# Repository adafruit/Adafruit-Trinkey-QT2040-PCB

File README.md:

## Adafruit Trinkey QT2040 PCB

<a href="http://www.adafruit.com/products/5056"><br/>
Click here to purchase one from the Adafruit shop</a>

PCB files for the Adafruit Trinkey QT2040. 

Format is EagleCAD schematic and board layout
* https://www.adafruit.com/product/5056

### Description

It's half USB Key, half Adafruit QT Py, and a lotta RP2040...it's Trinkey QT2040, the circuit board with an RP2040 heart and Stemma QT legs. Folks are loving the QT Py 2040 we made, but maybe you want something plug-and-play. So we thought, hey what if we made something like that plugs right into your computer's USB port? And this is what we came up with!

The PCB is designed to slip into any USB A port on a computer or laptop. There's an RP2040 microcontroller on board with just enough circuitry to keep it happy. There's an RGB NeoPixel, a reset and bootloader or user button and a STEMMA QT Port on the end. That's it!

With the body of the board being 1.0" x 0.7" and four mounting holes, you can attach just about any of our QT boards right on (some are a little larger so just check that has the holes in the same locations). Use M2.5 sized standoffs and screws to do so, you could use 2 diagonal at a minimum. Then use a shorty QT cable and you've got a custom sensor Trinkey for any sensor purpose.

The board comes with 8 MB of QSPI flash memory so you can put all of our CircuitPython drivers on the disk!

#### Plug-and-play STEMMA QT

One of the stars of this board is our favorite connector - the STEMMA QT, a chainable I2C port that can be used with any of our STEMMA QT sensors and accessories. Having this connector means you don't need to do any soldering to get started.

What can you pop into the QT port? How about OLEDs! Inertial Measurement Units! Sensors a-plenty. All plug-and-play thanks to the innovative chainable design: SparkFun Qwiic-compatible STEMMA QT connectors for the I2C bus so you don't even need to solder. Just plug in a compatible cable and attach it to your MCU of choice, and you’re ready to load up some software and measure some light.

Use any SparkFun Qwiic boards! Seeed Grove I2C boards will also work with this adapter cable.

#### Software Support

At the time of launch, there is no Arduino core support for the chip on this board. There is great C/C++ support, an official MicroPython port, and a CircuitPython port! We of course recommend CircuitPython because we think it's the easiest way to get started and it has support with most of our drivers, displays, sensors, and more, supported out of the box so you can follow along with our CircuitPython projects and tutorials.

While the RP2040 has lots of onboard RAM (264KB), it does not have built-in FLASH memory. Instead, that is provided by the external QSPI flash chip. On this board there is 8MB, which is shared between the program it's running and any file storage used by MicroPython or CircuitPython. When using C/C++ you get the whole flash memory, if using Python you will have about 7 MB remaining for code, files, images, fonts, etc.

* Main body is same size/mounting holes as most of our Stemma QT boards (1.0" x 0.7" with M2.5 holes)
* USB Type A connector with extra-thick PCB to fit into a USB host port
* RP2040 32-bit Cortex M0+ dual-core running at ~125 MHz @ 3.3V logic and power
* 264 KB RAM
* 8 MB SPI FLASH chip for storing files and CircuitPython/MicroPython code storage. No EEPROM
* Native USB supported by every OS - can be used as USB serial console, MIDI, Keyboard/Mouse HID, even a little disk drive for storing Python scripts.
* Can be used with MicroPython or CircuitPython
* Built-in RGB NeoPixel LED
* STEMMA QT / Qwiic port for I2C connectivity
* 3.3V regulator with 600mA peak output
* 12 MHz crystal
* Both Reset button and Bootloader select buttons for quick restarts (no unplugging-replugging to relaunch code)
* Bootloader button can also be safely used in 'user' code

#### About the RP2040

Inside the RP2040 is a 'permanent ROM' USB UF2 bootloader. What that means is when you want to program new firmware, you can hold down the BOOT button while plugging it into USB (or pulling down the RUN/Reset pin to ground) and it will appear as a USB disk drive you can drag the firmware onto. Folks who have been using Adafruit products will find this very familiar - we use the technique on all our native-USB boards. Just note you don't double-click reset, instead hold down the BOOT button during boot to enter the bootloader!

The RP2040 is a powerful chip, which has the clock speed of our M4 (SAMD51), and two cores that are equivalent to our M0 (SAMD21). Since it is an M0 chip, it does not have a floating point unit or DSP hardware support - so if you're doing something with heavy floating point math, it will be done in software and thus not as fast as an M4. For many other computational tasks, you'll get close-to-M4 speeds!

### License

Adafruit invests time and resources providing this open source design, please support Adafruit and open-source hardware by purchasing products from [Adafruit](https://www.adafruit.com)!

Designed by Limor Fried/Ladyada for Adafruit Industries.

Creative Commons Attribution/Share-Alike, all text above must be included in any redistribution. 
See license.txt for additional details.

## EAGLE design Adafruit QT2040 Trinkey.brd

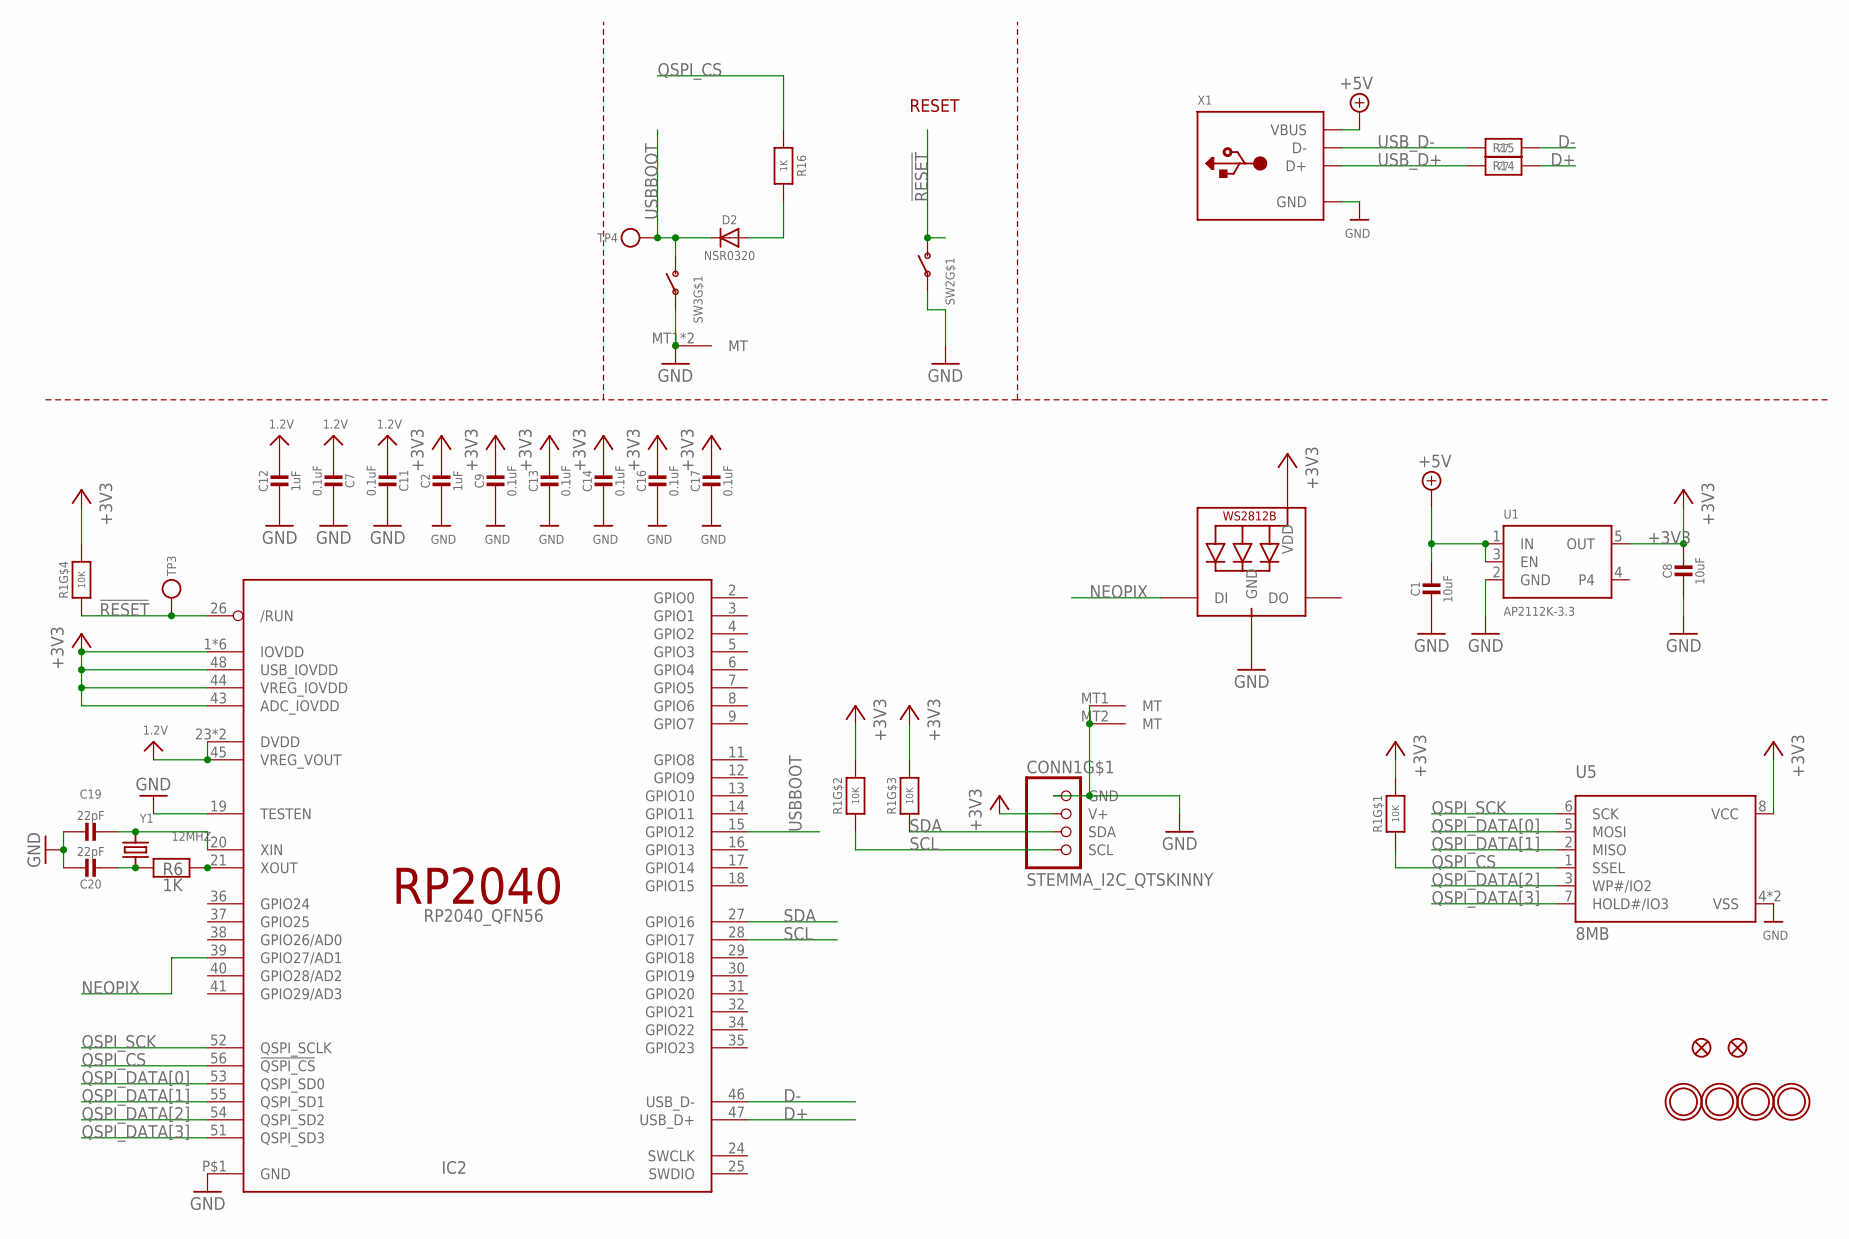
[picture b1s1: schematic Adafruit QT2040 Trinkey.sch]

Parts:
C1, C8: 10uF; 0805-NO
C2, C12: 1uF; 0603-NO
C7: 0.1uF; _0603MP
C9, C11, C13, C14, C16, C17: 0.1uF; 0603-NO
C19, C20: 22pF; 0603-NO
CONN1: STEMMA_I2C_QTSKINNY; JST_SH4_SKINNY
D2: NSR0320; SOD-323_MINI
IC2: RP2040_QFN56; QFN56_7MM_REDUCEDEPAD
LED1: WS2812B_SK6805_1515; SK6805_1515
R1: 10K; RESPACK_4X0603
R6, R16: 1K; 0603-NO
R14, R15: 27; 0603-NO
SW2, SW3: SWITCH_SPST_TACT_RA; SPST_TACTILE_RA
TP3, TP4: TESTPOINTROUND1.5MMNO; TESTPOINT_ROUND_1.5MM_NO
U1: AP2112K-3.3; SOT23-5
U5: 8MB; USON8_4X4
U$1, U$2, U$4, U$5: MOUNTINGHOLE2.5; MOUNTINGHOLE_2.5_PLATED
U$6, U$8: FIDUCIAL_1MM
X1: USB_TYPEAPCB; USBA_PCB
Y1: 12MHZ; CRYSTAL_2.5X2

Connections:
1.2V: C7.2, C11.2, C12.1, IC2.23 (DVDD), IC2.45 (VREG_VOUT), IC2.50 (DVDD)
!RESET: IC2.26 (/RUN), R1.4 (1), SW2.2 (S), TP3.P$1
+3V3: C2.1, C8.1, C9.1, C13.1, C14.1, C16.1, C17.1, CONN1.2 (V+), IC2.1 (IOVDD), IC2.10 (IOVDD), IC2.22 (IOVDD), IC2.33 (IOVDD), IC2.42 (IOVDD), IC2.43 (ADC_IOVDD), IC2.44 (VREG_IOVDD), IC2.48 (USB_IOVDD), IC2.49 (IOVDD), LED1.2 (VDD), R1.5 (2), R1.6 (2), R1.7 (2), R1.8 (2), U1.5 (OUT), U5.8 (VCC)
+5V: C1.1, U1.1 (IN), U1.3 (EN), X1.VCC (VBUS)
D+: IC2.47 (USB_D+), R15.2
D-: IC2.46 (USB_D-), R14.2
GND: C1.2, C2.2, C7.1, C8.2, C9.2, C11.1, C12.2, C13.2, C14.2, C16.2, C17.2, C19.1, C20.1, CONN1.1 (GND), CONN1.MT1 (MT), CONN1.MT2 (MT), IC2.19 (TESTEN), IC2.P$1 (GND), LED1.4 (GND), SW2.1, SW3.1, SW3.MT1 (MT), SW3.MT2 (MT), U1.2 (GND), U5.4 (VSS), U5.PAD (VSS), X1.GND
unnamed: D2.A, R16.2
unnamed: C19.2, IC2.20 (XIN), Y1.3 (2)
unnamed: C20.2, R6.1, Y1.1
unnamed: IC2.21 (XOUT), R6.2
NEOPIX: IC2.39 (GPIO27/AD1), LED1.1 (DI)
QSPI_CS: IC2.56 (!QSPI_CS), R1.1, R16.1, U5.1 (SSEL)
QSPI_DATA[0]: IC2.53 (QSPI_SD0), U5.5 (MOSI)
QSPI_DATA[1]: IC2.55 (QSPI_SD1), U5.2 (MISO)
QSPI_DATA[2]: IC2.54 (QSPI_SD2), U5.3 (WP#/IO2)
QSPI_DATA[3]: IC2.51 (QSPI_SD3), U5.7 (HOLD#/IO3)
QSPI_SCK: IC2.52 (QSPI_SCLK), U5.6 (SCK)
SCL: CONN1.4 (SCL), IC2.28 (GPIO17), R1.2 (1)
SDA: CONN1.3 (SDA), IC2.27 (GPIO16), R1.3 (1)
USBBOOT: D2.C, IC2.15 (GPIO12), SW3.2 (S), TP4.P$1
USB_D+: R15.1, X1.USB_PLUS (D+)
USB_D-: R14.1, X1.USB_NEG (D-)

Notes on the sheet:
RESET

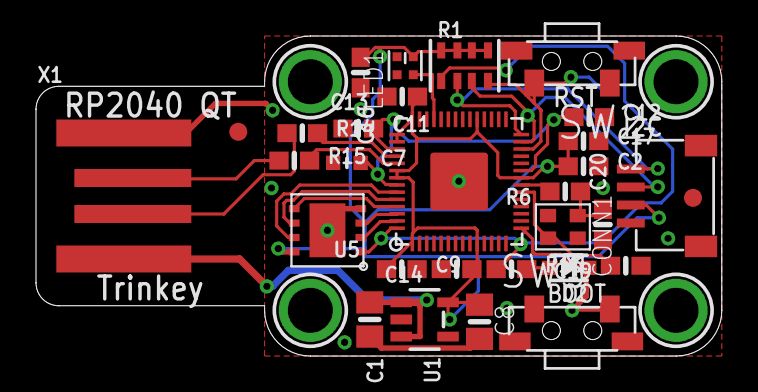
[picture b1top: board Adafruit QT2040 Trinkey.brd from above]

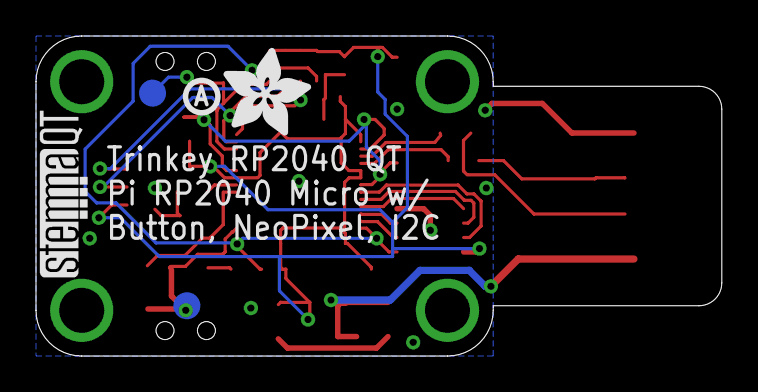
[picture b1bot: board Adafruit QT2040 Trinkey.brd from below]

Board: 2 copper layers, 38.1 x 17.8 mm, 39 parts (5 on the bottom side), 23 nets.

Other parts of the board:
U$7: STEMMAQT
U$9: PCBFEAT-REV-040
U$10: ADAFRUIT_5MM

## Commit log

2021-06-17 Add board files.
2021-06-22 Add pinout image.

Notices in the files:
parts and their libraries:
microbuilder: This work is placed in the public domain, and may be freely used for commercial and non-commercial work with the following conditions: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
